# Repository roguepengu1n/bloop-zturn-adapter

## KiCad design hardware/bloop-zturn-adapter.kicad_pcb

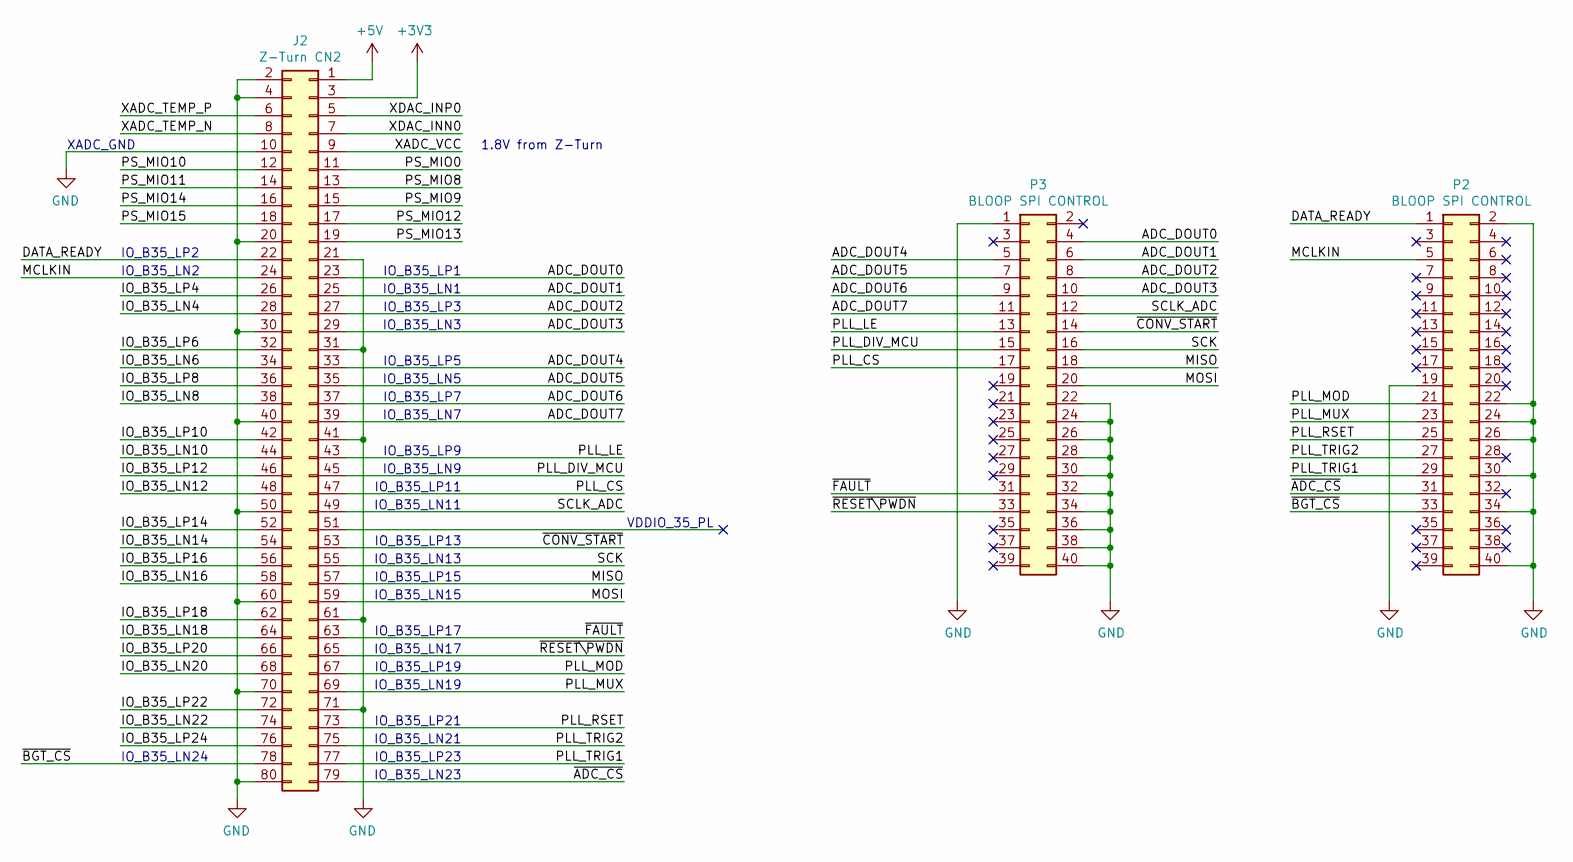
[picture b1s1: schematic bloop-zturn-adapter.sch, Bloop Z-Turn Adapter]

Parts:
J2: Z-Turn CN2; PinHeader_2x40_P1.27mm_Vertical_SMD; MPN 20021111-00080T4LF
P2, P3: BLOOP SPI CONTROL; PinHeader_2x20_P2.54mm_Vertical_SMD

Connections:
+3V3: J2.3
+5V: J2.1
/ADC_DOUT0: J2.23, P3.4
/ADC_DOUT1: J2.25, P3.6
/ADC_DOUT2: J2.27, P3.8
/ADC_DOUT3: J2.29, P3.10
/ADC_DOUT4: J2.33, P3.5
/ADC_DOUT5: J2.35, P3.7
/ADC_DOUT6: J2.37, P3.9
/ADC_DOUT7: J2.39, P3.11
/DATA_READY: J2.22, P2.1
/IO_B35_LN4: J2.28
/IO_B35_LN6: J2.34
/IO_B35_LN8: J2.38
/IO_B35_LN10: J2.44
/IO_B35_LN12: J2.48
/IO_B35_LN14: J2.54
/IO_B35_LN16: J2.58
/IO_B35_LN18: J2.64
/IO_B35_LN20: J2.68
/IO_B35_LN22: J2.74
/IO_B35_LP4: J2.26
/IO_B35_LP6: J2.32
/IO_B35_LP8: J2.36
/IO_B35_LP10: J2.42
/IO_B35_LP12: J2.46
/IO_B35_LP14: J2.52
/IO_B35_LP16: J2.56
/IO_B35_LP18: J2.62
/IO_B35_LP20: J2.66
/IO_B35_LP22: J2.72
/IO_B35_LP24: J2.76
/MCLKIN: J2.24, P2.5
/MISO: J2.57, P3.18
/MOSI: J2.59, P3.20
/PLL_CS: J2.47, P3.17
/PLL_DIV_MCU: J2.45, P3.15
/PLL_LE: J2.43, P3.13
/PLL_MOD: J2.67, P2.21
/PLL_MUX: J2.69, P2.23
/PLL_RSET: J2.73, P2.25
/PLL_TRIG1: J2.77, P2.29
/PLL_TRIG2: J2.75, P2.27
/PS_MIO0: J2.11
/PS_MIO8: J2.13
/PS_MIO9: J2.15
/PS_MIO10: J2.12
/PS_MIO11: J2.14
/PS_MIO12: J2.17
/PS_MIO13: J2.19
/PS_MIO14: J2.16
/PS_MIO15: J2.18
/SCK: J2.55, P3.16
/SCLK_ADC: J2.49, P3.12
/XADC_TEMP_N: J2.8
/XADC_TEMP_P: J2.6
/XADC_VCC: J2.9
/XDAC_INN0: J2.7
/XDAC_INP0: J2.5
/~ADC_CS: J2.79, P2.31
/~BGT_CS: J2.78, P2.33
/~CONV_START: J2.53, P3.14
/~FAULT: J2.63, P3.31
/~RESET\PWDN: J2.65, P3.33
GND: J2.2, J2.4, J2.10, J2.20, J2.21, J2.30, J2.31, J2.40, J2.41, J2.50, J2.60, J2.61, J2.70, J2.71, J2.80, P2.2, P2.19, P2.22, P2.24, P2.26, P2.30, P2.34, P2.40, P3.1, P3.22, P3.24, P3.26, P3.28, P3.30, P3.32, P3.34, P3.36, P3.38, P3.40

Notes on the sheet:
XADC_GND
VDDIO_35_PL
1.8V from Z-Turn
IO_B35_LP1
IO_B35_LN1
IO_B35_LP3
IO_B35_LN3
IO_B35_LP5
IO_B35_LN5
IO_B35_LP7
IO_B35_LN7
IO_B35_LP9
IO_B35_LN9
IO_B35_LP11
IO_B35_LN11
IO_B35_LP13
IO_B35_LN13
IO_B35_LP15
IO_B35_LN15
IO_B35_LP17
IO_B35_LN17
IO_B35_LP19
IO_B35_LN19
IO_B35_LP21
IO_B35_LN21
IO_B35_LP23
IO_B35_LN23
IO_B35_LP2
IO_B35_LN2
IO_B35_LN24

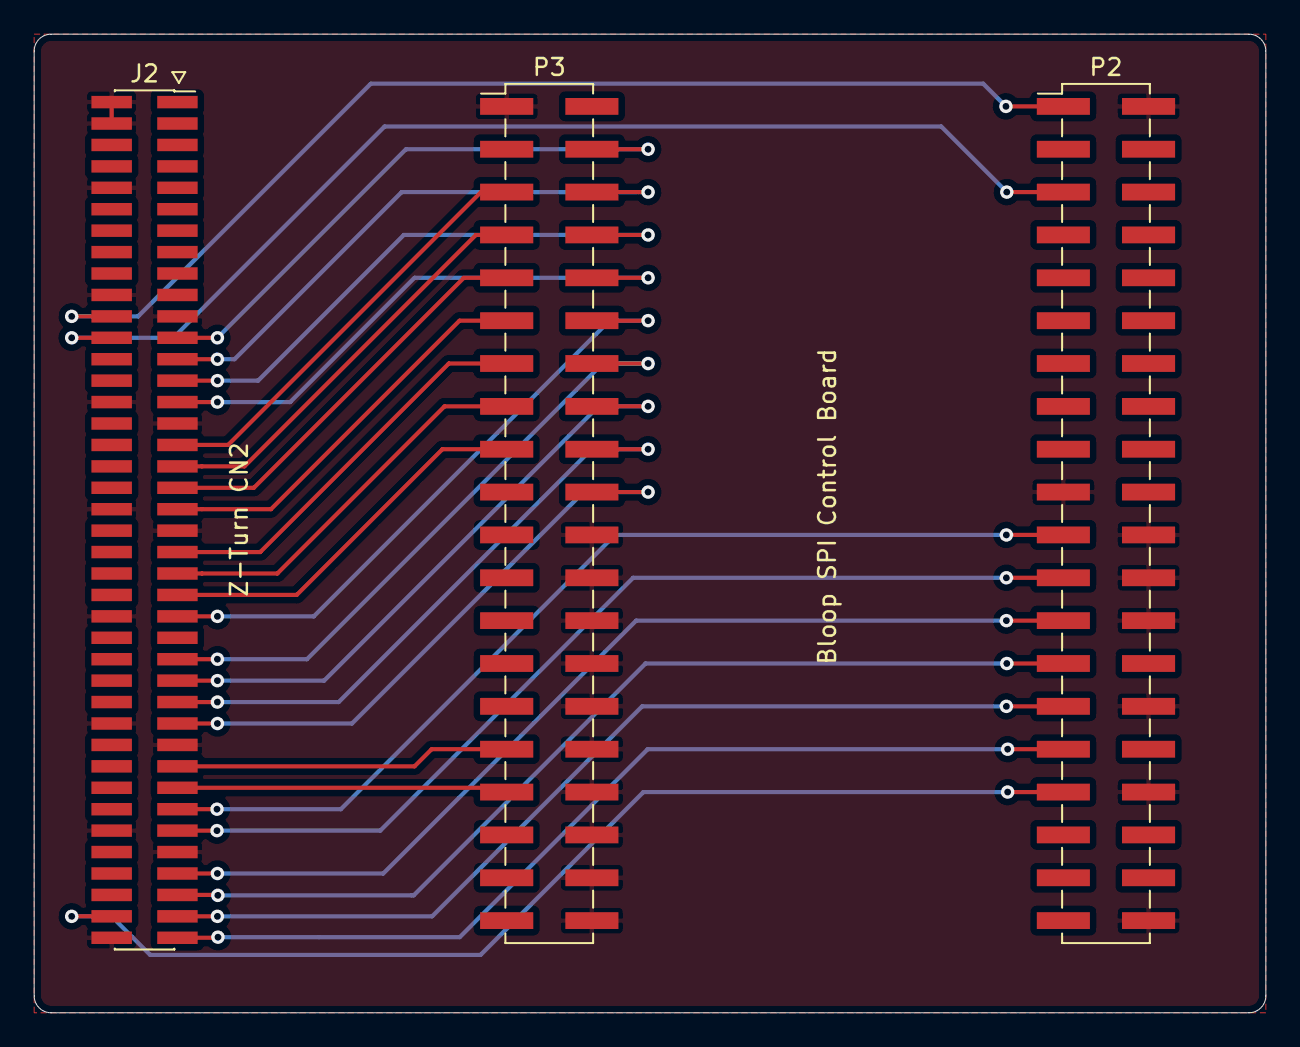
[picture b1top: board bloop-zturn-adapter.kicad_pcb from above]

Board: 2 copper layers, 73.0 x 58.0 mm, 3 parts (0 on the bottom side), 28 nets.

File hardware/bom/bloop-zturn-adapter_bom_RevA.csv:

Component,Description,Part,References,Value,Footprint,Quantity Per PCB,Datasheet,MPN
1,"Generic connector, double row, 02x40, odd/even pin numbering scheme (row 1 odd numbers, row 2 even numbers), script generated (kicad-library-utils/schlib/autogen/connector/)",Conn_02x40_Odd_Even,J2,Z-Turn CN2,PinHeader_2x40_P1.27mm_Vertical_SMD,1,https://cdn.amphenol-icc.com/media/wysiwyg/files/drawing/200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,20021111-00080T4LF
2,"Generic connector, double row, 02x20, odd/even pin numbering scheme (row 1 odd numbers, row 2 even numbers), script generated (kicad-library-utils/schlib/autogen/connector/)",Conn_02x20_Odd_Even,P2 P3,BLOOP SPI CONTROL,PinHeader_2x20_P2.54mm_Vertical_SMD,2,https://cdn.amphenol-icc.com/media/wysiwyg/files/drawing/95157.pdf,95157-140LF





Component Groups:,2
Component Count:,3
Fitted Components:,3
Number of PCBs:,1
Total components:,3
Schematic Version:,Rev A
Schematic Date:,2020-01-12
PCB Variant:,[u'default']
BoM Date:,Sun 12 Jan 2020 03:46:34 PM CST
Schematic Source:,/home/leo/projects/bloop-zturn-adapter/hardware/bloop-zturn-adapter.sch
KiCad Version:,Eeschema 5.1.5-52549c5~84~ubuntu18.04.1

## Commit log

2020-01-11 Completed schematic
2020-01-12 Schematic edits to make layout routing easier and completed layout. Generated gerbers and pdf schematic.
2020-01-12 Create LICENSE
2020-01-12 Generated BOM
